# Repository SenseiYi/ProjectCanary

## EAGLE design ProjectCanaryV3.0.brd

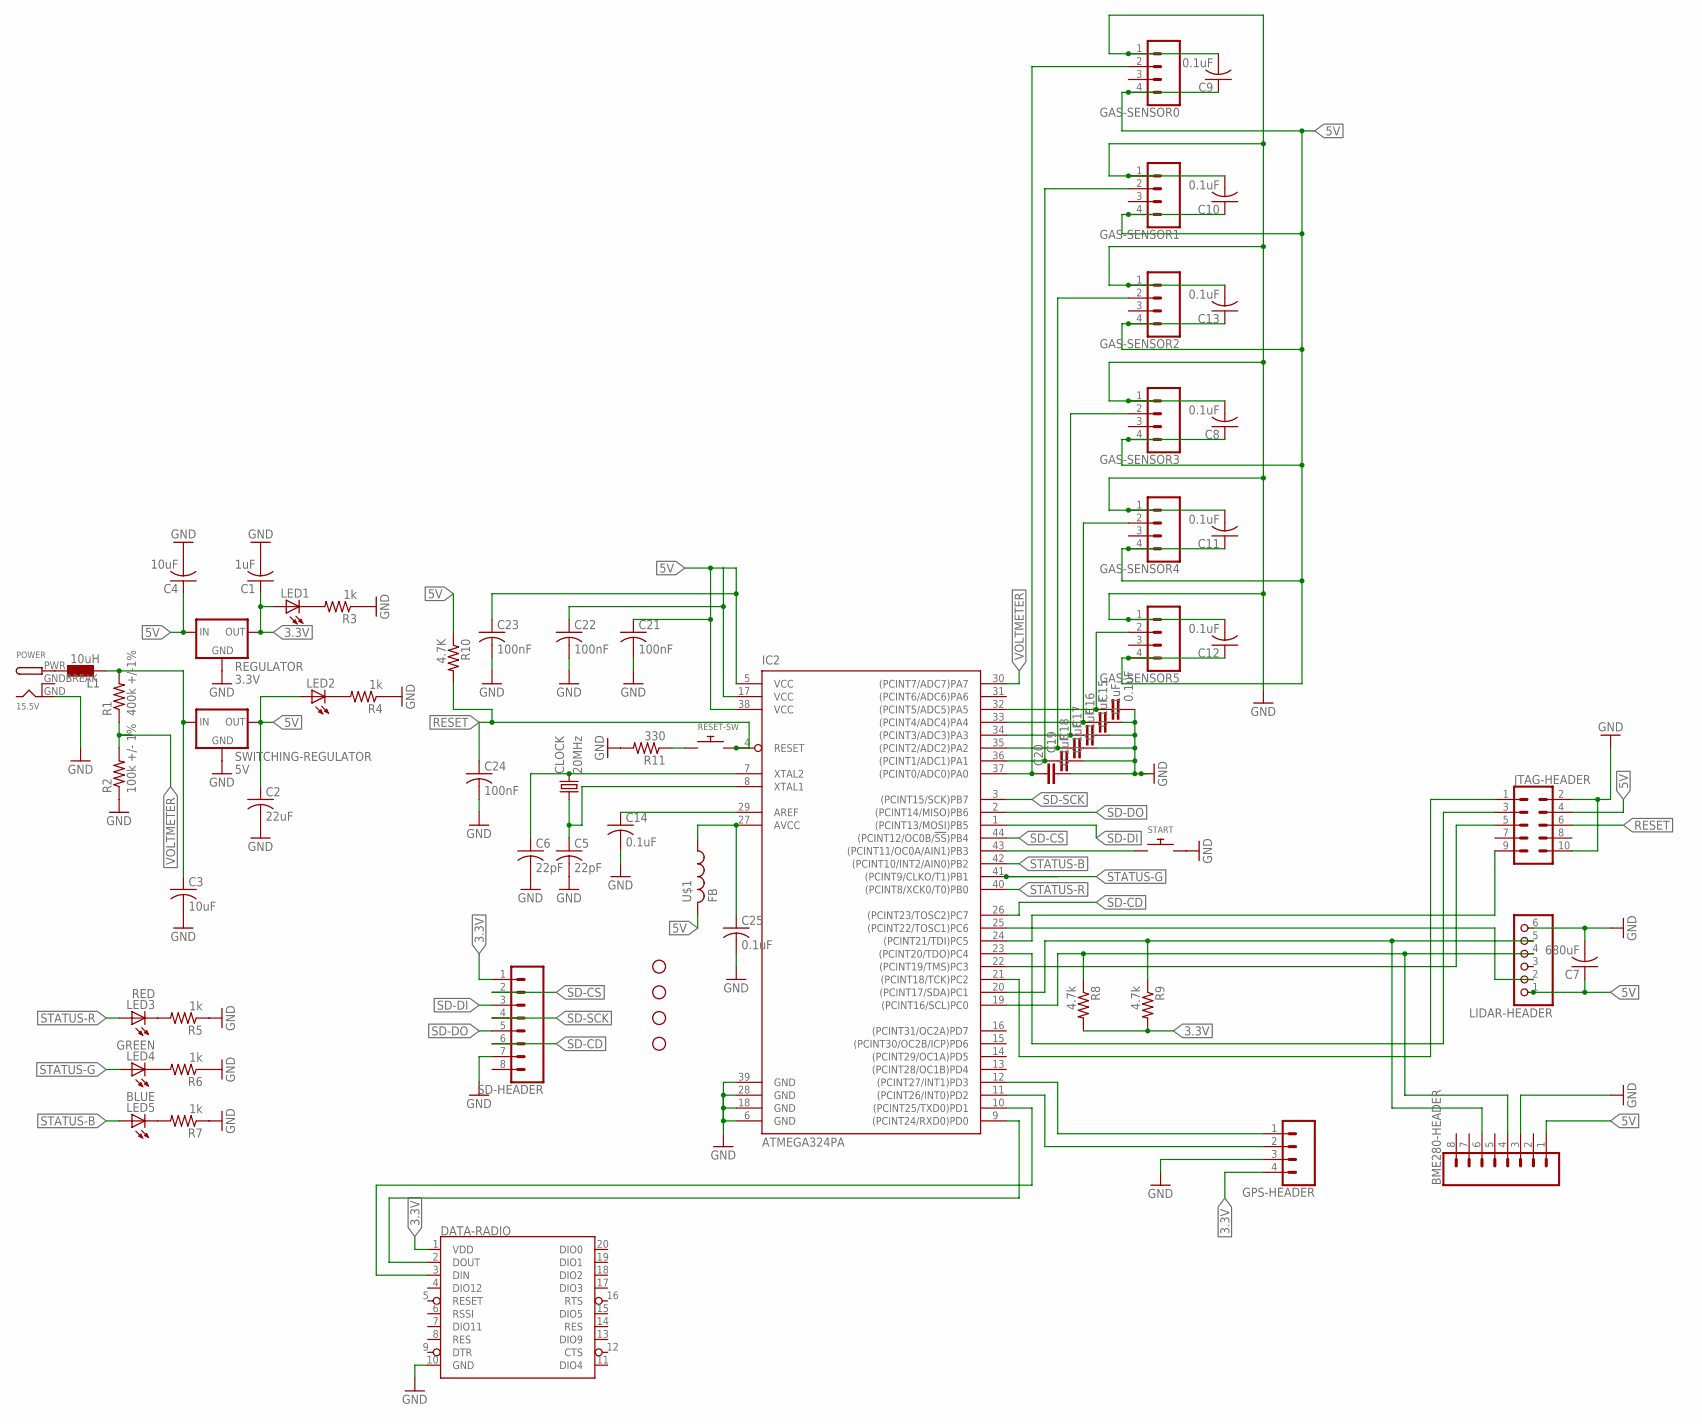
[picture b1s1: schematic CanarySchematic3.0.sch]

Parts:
BME280-HEADER: CONN_08"; 1X08
C1: 1uF; C0805
C2: 22uF; C0805
C3, C4: 10uF; C0805
C5, C6: 22pF; C0805
C7: 680uF; C0805
C8, C9, C10, C11, C12, C13, C14, C25: 0.1uF; C0805
C15, C16, C17, C18, C19, C20: 0.1uF; C0504
C21, C22, C23, C24: 100nF; C0805
CLOCK: 20MHz; 86SMX
DATA-RADIO: XBEE
GAS-SENSOR0, GAS-SENSOR1, GAS-SENSOR2, GAS-SENSOR3, GAS-SENSOR4, GAS-SENSOR5: CONN_04; 1X04
GPS-HEADER: CONN_04; 1X04
H8: STAND-OFF
IC2: ATMEGA324PA; TQFP44
JTAG-HEADER: CONN_05X2PTH; 2X5
L1: 10uH; L1812
LED1, LED2: LEDCHIP-LED0805; CHIP-LED0805
LED3: RED; CHIP-LED0805
LED4: GREEN; CHIP-LED0805
LED5: BLUE; CHIP-LED0805
LIDAR-HEADER: PINHD-1X6; 1X06
MOUNT-HOLE1, MOUNT-HOLE2, MOUNT-HOLE3: STAND-OFF
POWER: 15.5V; DCJACK_2MM_PTH
R1: 400k +/-1%; M0805
R2: 100k +/- 1%; M0805
R3, R4, R5, R6, R7: 1k; M0805
R8, R9: 4.7k; M0805
R10: 4.7K; M0805
R11: 330; M0805
REGULATOR: 3.3V; TO220-IGO
RESET-SW: SWITCH_PUSHBUTTONSOFTTOUCHSMD_SJ; PUSHBUTTON_SMD_SJ
SD-HEADER: CONN_08"; 1X08
START: SWITCH_PUSHBUTTONSOFTTOUCHSMD_SJ; PUSHBUTTON_SMD_SJ
SWITCHING-REGULATOR: 5V; TO220-IGO
U$1: FB

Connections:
3.3V: C1.1, DATA-RADIO.1 (VDD), GPS-HEADER.4, LED1.A, R8.2, R9.2, REGULATOR.OUT, SD-HEADER.1
5V: BME280-HEADER.1, C2.1, C4.1, C7.1, C8.1, C9.1, C10.1, C11.1, C12.1, C13.1, C25.1, GAS-SENSOR0.4, GAS-SENSOR1.4, GAS-SENSOR2.4, GAS-SENSOR3.4, GAS-SENSOR4.4, GAS-SENSOR5.4, IC2.27 (AVCC), JTAG-HEADER.4, LED2.A, LIDAR-HEADER.1, REGULATOR.IN, SWITCHING-REGULATOR.OUT, U$1.P$1 (1)
GND: BME280-HEADER.3, C1.2, C2.2, C3.2, C4.2, C5.2, C6.2, C7.2, C8.2, C9.2, C10.2, C11.2, C12.2, C13.2, C14.2, C15.2, C16.2, C17.2, C18.2, C19.2, C20.2, C21.2, C22.2, C23.2, C24.2, C25.2, DATA-RADIO.10 (GND), GAS-SENSOR0.1, GAS-SENSOR1.1, GAS-SENSOR2.1, GAS-SENSOR3.1, GAS-SENSOR4.1, GAS-SENSOR5.1, GPS-HEADER.3, IC2.6 (GND), IC2.18 (GND), IC2.28 (GND), IC2.39 (GND), JTAG-HEADER.2, JTAG-HEADER.10, LIDAR-HEADER.6, POWER.GND, R2.1, R3.1, R4.1, R5.1, R6.1, R7.1, R11.2, REGULATOR.GND, SD-HEADER.7, START.P$2, SWITCHING-REGULATOR.GND
GNDBREAK: POWER.GNDBREAK
unnamed: C3.1, L1.2, R1.2, SWITCHING-REGULATOR.IN
unnamed: LED1.C, R3.2
unnamed: LED2.C, R4.2
unnamed: LED3.C, R5.2
unnamed: LED4.C, R6.2
unnamed: LED5.C, R7.2
unnamed: IC2.43 ((PCINT11/OC0A/AIN1)PB3), START.P$1
unnamed: C6.1, CLOCK.4 (2), IC2.7 (XTAL2)
unnamed: GPS-HEADER.1, IC2.12 ((PCINT27/INT1)PD3)
unnamed: GPS-HEADER.2, IC2.11 ((PCINT26/INT0)PD2)
unnamed: C20.1, GAS-SENSOR0.2, IC2.37 ((PCINT0/ADC0)PA0)
unnamed: IC2.25 ((PCINT22/TOSC1)PC6), LIDAR-HEADER.2
unnamed: IC2.24 ((PCINT21/TDI)PC5), JTAG-HEADER.9
unnamed: C14.1, IC2.29 (AREF)
unnamed: C19.1, GAS-SENSOR1.2, IC2.36 ((PCINT1/ADC1)PA1)
unnamed: C18.1, GAS-SENSOR2.2, IC2.35 ((PCINT2/ADC2)PA2)
unnamed: C17.1, GAS-SENSOR3.2, IC2.34 ((PCINT3/ADC3)PA3)
unnamed: C16.1, GAS-SENSOR4.2, IC2.33 ((PCINT4/ADC4)PA4)
unnamed: C15.1, GAS-SENSOR5.2, IC2.32 ((PCINT5/ADC5)PA5)
unnamed: BME280-HEADER.4, IC2.19 ((PCINT16/SCL)PC0), LIDAR-HEADER.4, R8.1
unnamed: L1.1, POWER.PWR
unnamed: IC2.23 ((PCINT20/TDO)PC4), JTAG-HEADER.3
unnamed: BME280-HEADER.6, IC2.20 ((PCINT17/SDA)PC1), LIDAR-HEADER.5, R9.1
unnamed: IC2.22 ((PCINT19/TMS)PC3), JTAG-HEADER.5
unnamed: DATA-RADIO.3 (DIN), IC2.10 ((PCINT25/TXD0)PD1)
unnamed: DATA-RADIO.2 (DOUT), IC2.9 ((PCINT24/RXD0)PD0)
unnamed: IC2.21 ((PCINT18/TCK)PC2), JTAG-HEADER.1
unnamed: C21.1, C22.1, C23.1, IC2.5 (VCC), IC2.17 (VCC), IC2.38 (VCC)
unnamed: R11.1, RESET-SW.P$1
unnamed: C5.1, CLOCK.1, IC2.8 (XTAL1)
RESET: C24.1, IC2.4 (RESET), JTAG-HEADER.6, R10.2, RESET-SW.P$2
SD-CD: IC2.26 ((PCINT23/TOSC2)PC7), SD-HEADER.6
SD-CS: IC2.44 ((PCINT12/OC0B/!SS!)PB4), SD-HEADER.2
SD-DI: IC2.1 ((PCINT13/MOSI)PB5), SD-HEADER.3
SD-DO: IC2.2 ((PCINT14/MISO)PB6), SD-HEADER.5
SD-SCK: IC2.3 ((PCINT15/SCK)PB7), SD-HEADER.4
STATUS-B: IC2.42 ((PCINT10/INT2/AIN0)PB2), LED5.A
STATUS-G: IC2.41 ((PCINT9/CLKO/T1)PB1), LED4.A
STATUS-R: IC2.40 ((PCINT8/XCK0/T0)PB0), LED3.A
VOLTMETER: IC2.30 ((PCINT7/ADC7)PA7), R1.1, R2.2

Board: 2 copper layers, 65 parts (0 on the bottom side), 43 nets, no tracks yet.

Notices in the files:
parts and their libraries:
SparkFun-IC-Power: Licensing: Creative Commons ShareAlike 4.0 International - https://creativecommons.org/licenses/by-sa/4.0
